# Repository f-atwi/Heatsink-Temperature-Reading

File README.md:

# Heatsink_Temperature_Reading
A project to read temperature of a heatsink by 5 thermocouples and 3D visualize them on the computer.

The PCB design was made completely on Eagle. 
Custom packages for the AD8495 where created to make the board. The board was designed as a shield for the STM32 Nucleo F411RE and also compatible with Arduino boards. 
PDFs of the schematic and board as well as the PCB project files can be found.
The ciruit was designed to be powered completely by the Nucleo board. No external connections required.

The code for the STM32 Nucleo F411RE board was written on the STM32Cube IDE. 
The code initialized an ADC to read data from the designed shield, a DMA to transfer data from ADC to memory, and a UART to tranfer data to the PC.
The data read are also paired with a sensor ID for correct reading on the PC end.

Solidworks was used to model the heatsink. This model will be used by matlab to show temperatures as colors.

The Matlab code is where all the visualizing takes place.
Matlab takes the obj file of the model. 
It uses data received from UART to get the temperatures. The IDs transmitted with the temperatures helps pinpoint which sensor the data is from.
The data is hence displayed as color where blue is the coldest (minimum is 15°C) and red is the hottest (maximum 60°C).

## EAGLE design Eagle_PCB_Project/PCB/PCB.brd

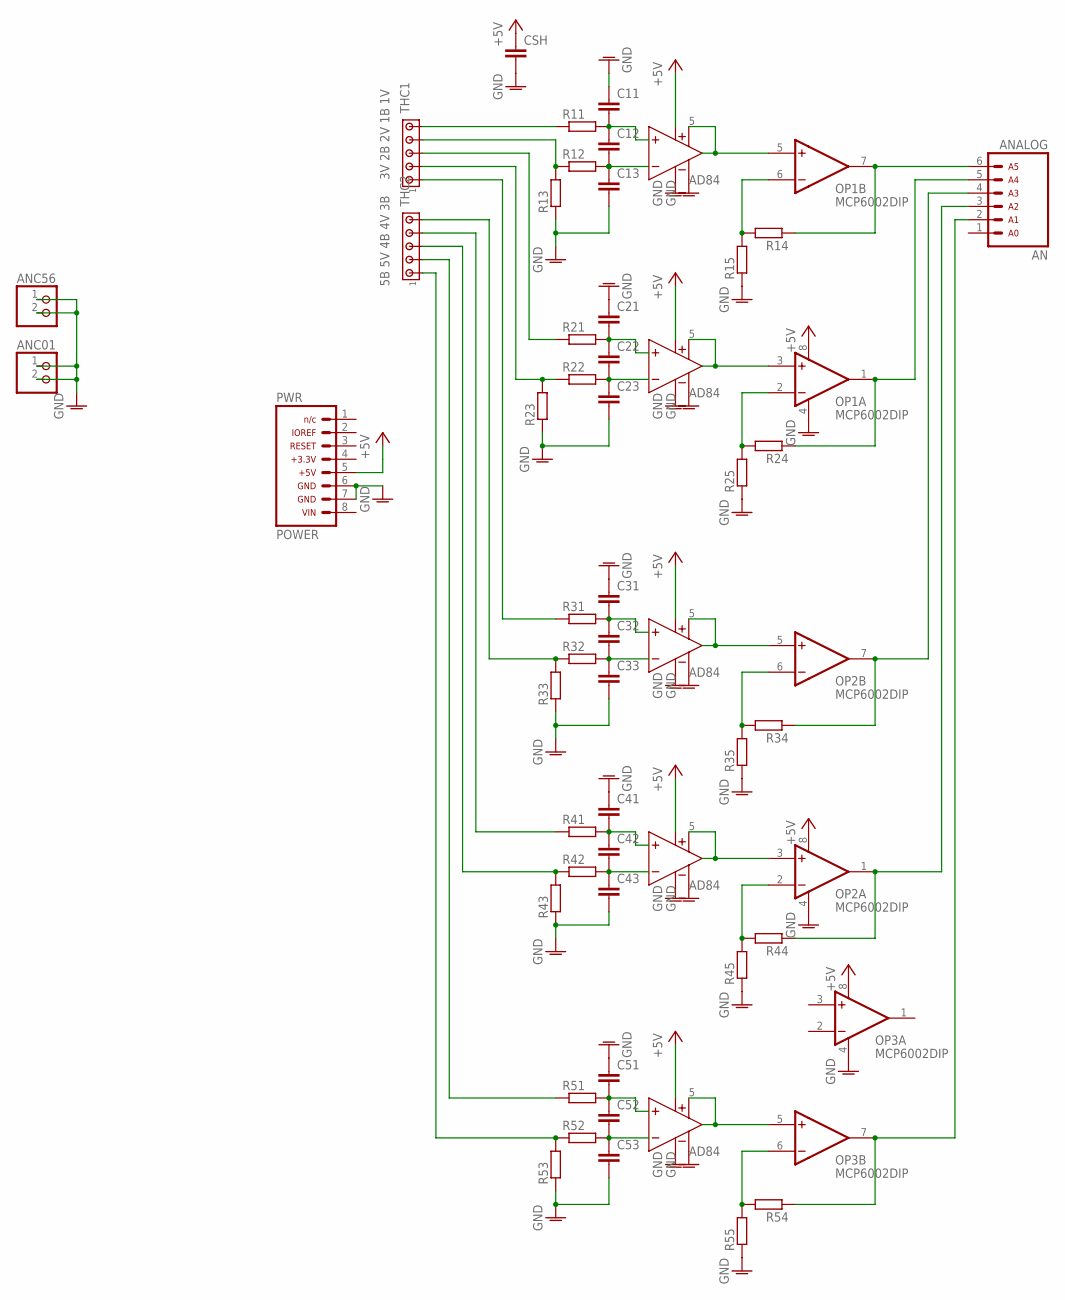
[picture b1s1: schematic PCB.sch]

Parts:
AN: ARDUINO_CONN-ANALOGSIP; CONN-1X06
ANC01, ANC56: PINHD-1X2; 1X02
C11, C12, C13, C21, C22, C23, C31, C32, C33, C41, C42, C43, C51, C52, C53: C-EU050-025X075; C050-025X075
CSH: C-EU050-025X075; C050-025X075
OP1, OP2, OP3: MCP6002DIP; DIP-8
PWR: ARDUINO_CONN-POWERSIP; CONN-1X08
R11, R12, R13, R14, R15, R21, R22, R23, R24, R25, R31, R32, R33, R34, R35, R41, R42, R43, R44, R45, R51, R52, R53, R54, R55: R-EU_0207/10; 0207/10
THC1: 3V 2B 2V 1B 1V; 10X05MTA
THC2: 5B 5V 4B 4V 3B; 10X05MTA
U$1, U$2, U$3, U$4, U$5: AD84; DIP-8

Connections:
+5V: CSH.1, OP1.8 (V+), OP2.8 (V+), OP3.8 (V+), PWR.5, U$1.7 (V+), U$2.7 (V+), U$3.7 (V+), U$4.7 (V+), U$5.7 (V+)
GNDA: ANC01.1, ANC01.2, ANC56.1, ANC56.2, C11.1, C13.2, C21.1, C23.2, C31.1, C33.2, C41.1, C43.2, C51.1, C53.2, CSH.2, OP1.4 (V-), OP2.4 (V-), OP3.4 (V-), PWR.6, PWR.7, R13.1, R15.1, R23.1, R25.1, R33.1, R35.1, R43.1, R45.1, R53.1, R55.1, U$1.2 (REF), U$1.3 (V-), U$2.2 (REF), U$2.3 (V-), U$3.2 (REF), U$3.3 (V-), U$4.2 (REF), U$4.3 (V-), U$5.2 (REF), U$5.3 (V-)
unnamed: OP1.5 (+IN), U$1.5 (SENS), U$1.6 (OUT)
unnamed: AN.6, OP1.7 (OUT), R14.1
unnamed: OP1.6 (-IN), R14.2, R15.2
unnamed: C11.2, C12.1, R11.2, U$1.8 (IN+)
unnamed: R12.1, R13.2, THC1.4
unnamed: C12.2, C13.1, R12.2, U$1.1 (IN-)
unnamed: R22.1, R23.2, THC1.2
unnamed: R32.1, R33.2, THC2.5
unnamed: OP1.2 (-IN), R24.2, R25.2
unnamed: C21.2, C22.1, R21.2, U$2.8 (IN+)
unnamed: C22.2, C23.1, R22.2, U$2.1 (IN-)
unnamed: AN.5, OP1.1 (OUT), R24.1
unnamed: OP1.3 (+IN), U$2.5 (SENS), U$2.6 (OUT)
unnamed: OP2.5 (+IN), U$3.5 (SENS), U$3.6 (OUT)
unnamed: OP2.6 (-IN), R34.2, R35.2
unnamed: C31.2, C32.1, R31.2, U$3.8 (IN+)
unnamed: C32.2, C33.1, R32.2, U$3.1 (IN-)
unnamed: AN.4, OP2.7 (OUT), R34.1
unnamed: R42.1, R43.2, THC2.3
unnamed: OP2.2 (-IN), R44.2, R45.2
unnamed: C41.2, C42.1, R41.2, U$4.8 (IN+)
unnamed: C42.2, C43.1, R42.2, U$4.1 (IN-)
unnamed: AN.3, OP2.1 (OUT), R44.1
unnamed: OP2.3 (+IN), U$4.5 (SENS), U$4.6 (OUT)
unnamed: R52.1, R53.2, THC2.1
unnamed: OP3.5 (+IN), U$5.5 (SENS), U$5.6 (OUT)
unnamed: OP3.6 (-IN), R54.2, R55.2
unnamed: C51.2, C52.1, R51.2, U$5.8 (IN+)
unnamed: C52.2, C53.1, R52.2, U$5.1 (IN-)
unnamed: AN.2, OP3.7 (OUT), R54.1
unnamed: R11.1, THC1.5
unnamed: R21.1, THC1.3
unnamed: R31.1, THC1.1
unnamed: R41.1, THC2.4
unnamed: R51.1, THC2.2

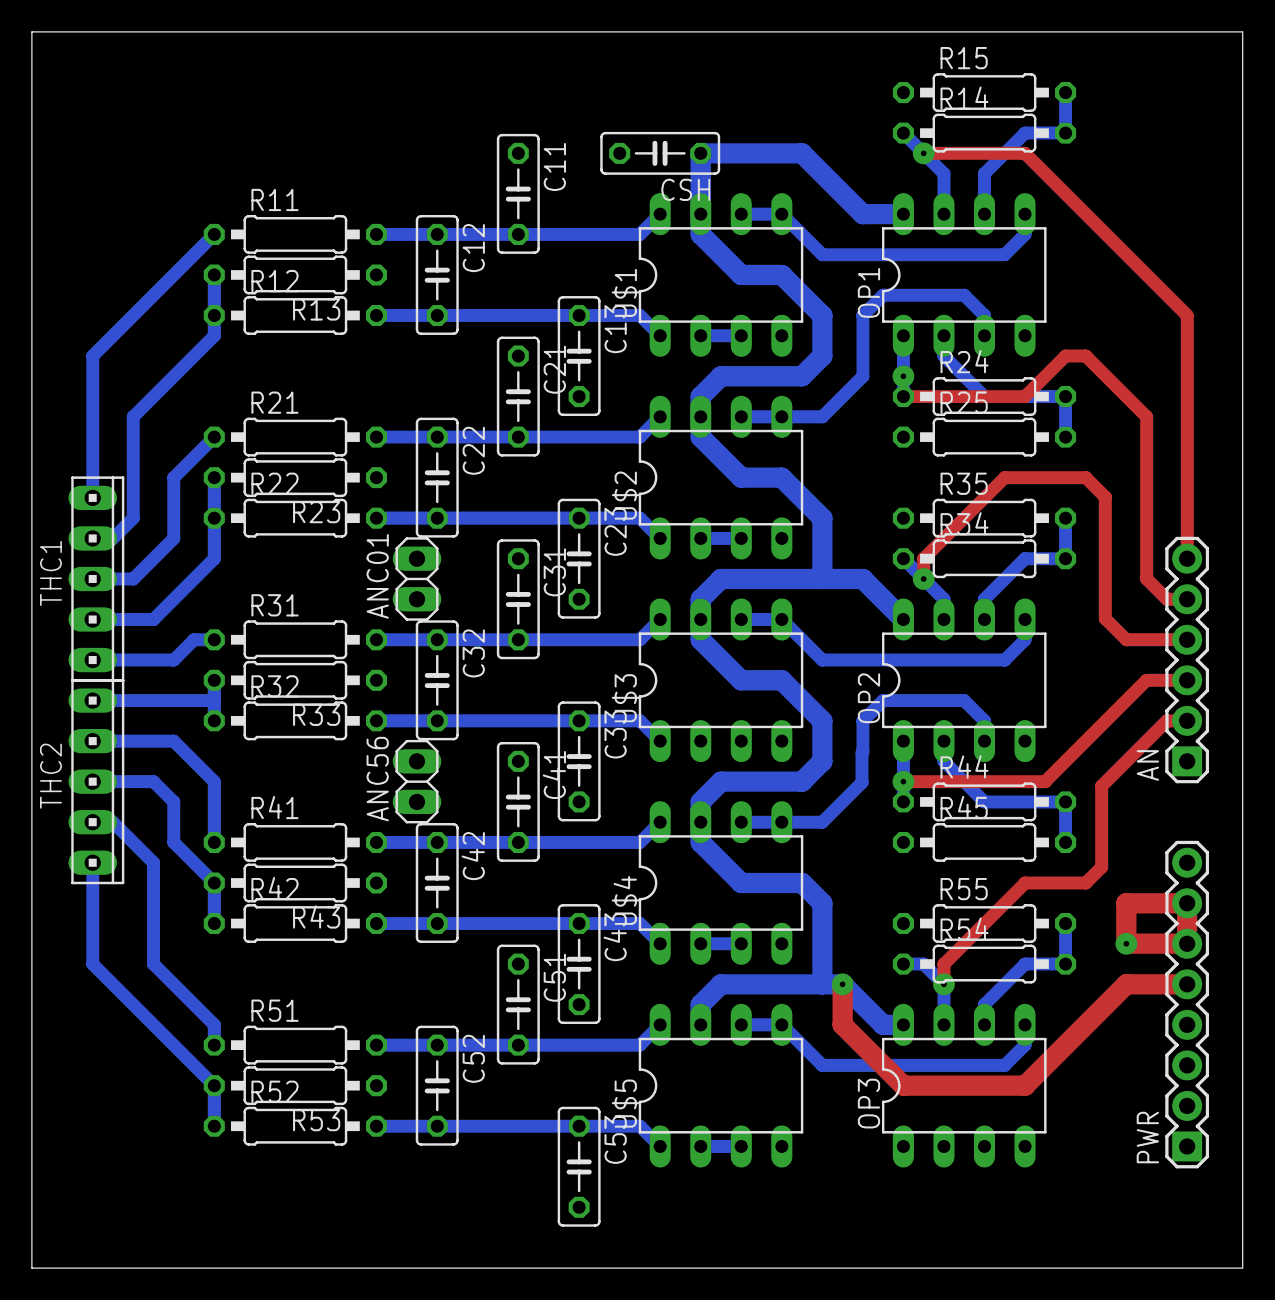
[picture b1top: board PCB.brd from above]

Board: 2 copper layers, 75.9 x 77.5 mm, 55 parts (0 on the bottom side), 37 nets.

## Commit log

2020-12-18 Add files via upload
    These are the Matlab files to read data sent by STM32 over UART. The code also displays the temperature as colors on a 3D model of the heatsink. The object to be displayed here is heatsink.obj.
